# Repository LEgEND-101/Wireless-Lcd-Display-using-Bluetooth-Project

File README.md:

# Wireless-Lcd-Display-using-Bluetooth-Project
This wireless LCD display shows information sent from a smartphone. The user can send text messages with up to 32 alphanumeric characters to the LCD within Bluetooth range of about 10 metres.

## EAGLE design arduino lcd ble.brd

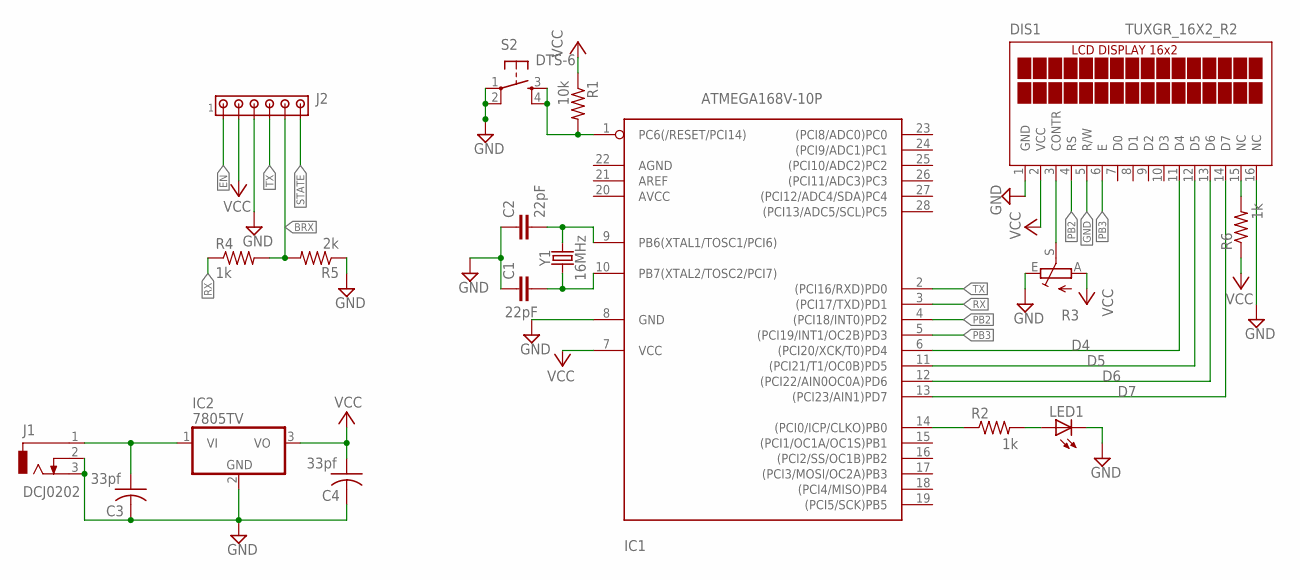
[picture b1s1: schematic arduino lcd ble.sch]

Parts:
C1, C2: 22pF; CAP-PTH-2.54
C3, C4: 33pf; C025-030X050
DIS1: TUXGR_16X2_R2
IC1: ATMEGA168V-10P; DIL28-3
IC2: 7805TV; TO220V
J1: DCJ0202
J2: MTA06-100; 10X06MTA
LED1: LED3MM
R1: 10k; 0204/7
R2, R4, R6: 1k; 0204/7
R3: TRIM_EU-CA6V; CA6V
R5: 2k; 0204/7
S2: DTS-6
Y1: 16MHz; HC49US

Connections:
BRX: J2.5, R4.2, R5.2
CONT: DIS1.3 (CONTR), R3.S
D4: DIS1.11 (D4), IC1.6 ((PCI20/XCK/T0)PD4)
D5: DIS1.12 (D5), IC1.11 ((PCI21/T1/OC0B)PD5)
D6: DIS1.13 (D6), IC1.12 ((PCI22/AIN0OC0A)PD6)
D7: DIS1.14 (D7), IC1.13 ((PCI23/AIN1)PD7)
EN: J2.1
GND: C1.1, C2.1, C3.2, C4.2, DIS1.1 (GND), DIS1.5 (R/W), DIS1.16 (NC), IC1.8 (GND), IC2.2 (GND), J1.2, J1.3, J2.3, LED1.K (C), R3.E, R5.1, S2.1, S2.2
unnamed: C2.2, IC1.9 (PB6(XTAL1/TOSC1/PCI6)), Y1.2
unnamed: C1.2, IC1.10 (PB7(XTAL2/TOSC2/PCI7)), Y1.1
unnamed: DIS1.15 (NC), R6.2
unnamed: IC1.14 ((PCI0/ICP/CLKO)PB0), R2.1
unnamed: LED1.A, R2.2
unnamed: C3.1, IC2.1 (VI), J1.1
unnamed: IC1.1 (PC6(/RESET/PCI14)), R1.2, S2.3, S2.4
PB2: DIS1.4 (RS), IC1.4 ((PCI18/INT0)PD2)
PB3: DIS1.6 (E), IC1.5 ((PCI19/INT1/OC2B)PD3)
RX: IC1.3 ((PCI17/TXD)PD1), R4.1
STATE: J2.6
TX: IC1.2 ((PCI16/RXD)PD0), J2.4
VCC: C4.1, DIS1.2 (VCC), IC1.7 (VCC), IC2.3 (VO), J2.2, R1.1, R3.A, R6.1

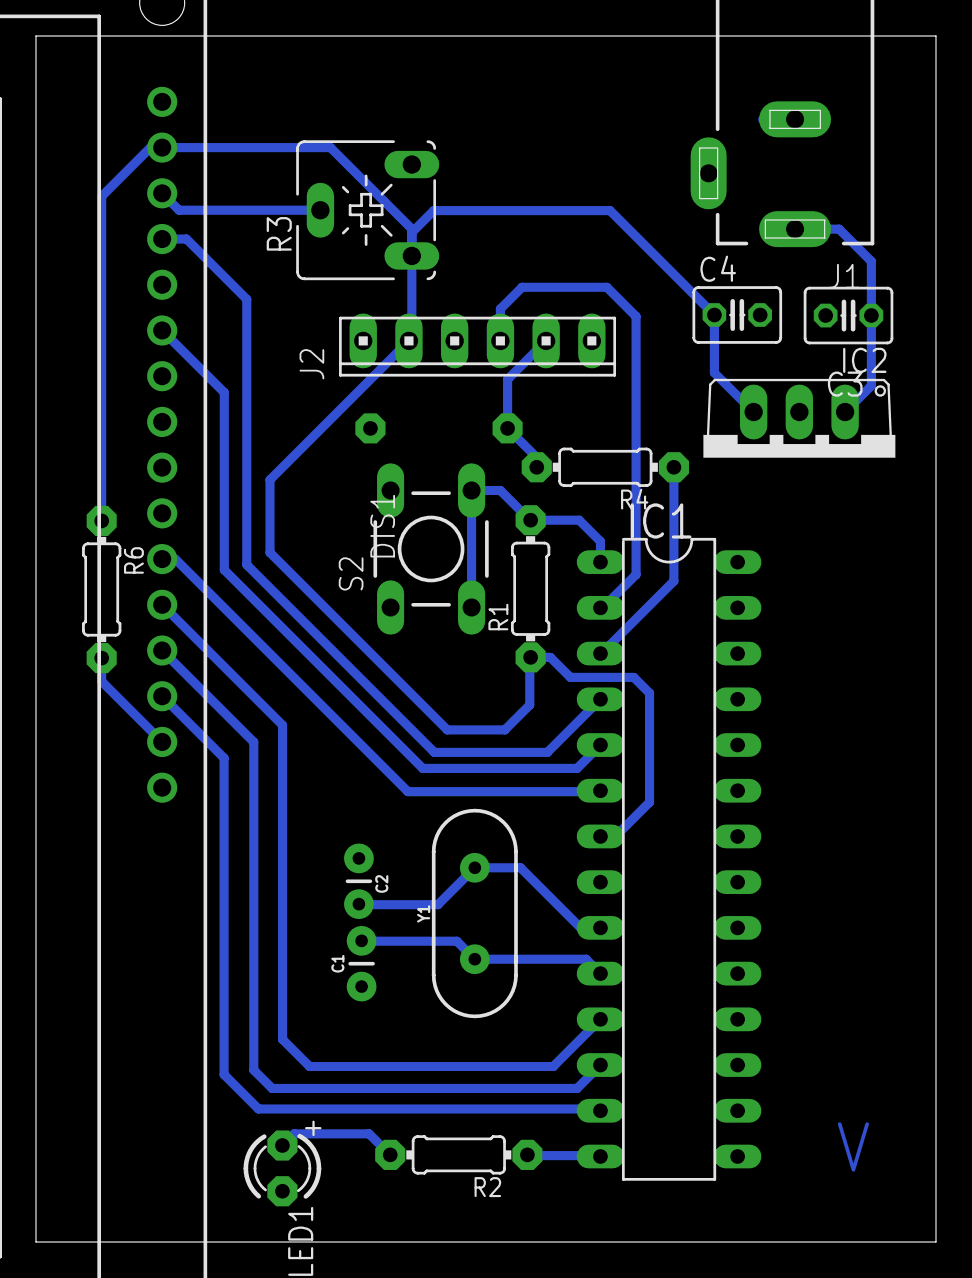
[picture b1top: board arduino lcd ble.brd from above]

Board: 2 copper layers, 50.0 x 67.0 mm, 18 parts (1 on the bottom side), 19 nets.

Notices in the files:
parts and their libraries:
SparkFun-Capacitors: Licensing: Creative Commons ShareAlike 4.0 International - https://creativecommons.org/licenses/by-sa/4.0
